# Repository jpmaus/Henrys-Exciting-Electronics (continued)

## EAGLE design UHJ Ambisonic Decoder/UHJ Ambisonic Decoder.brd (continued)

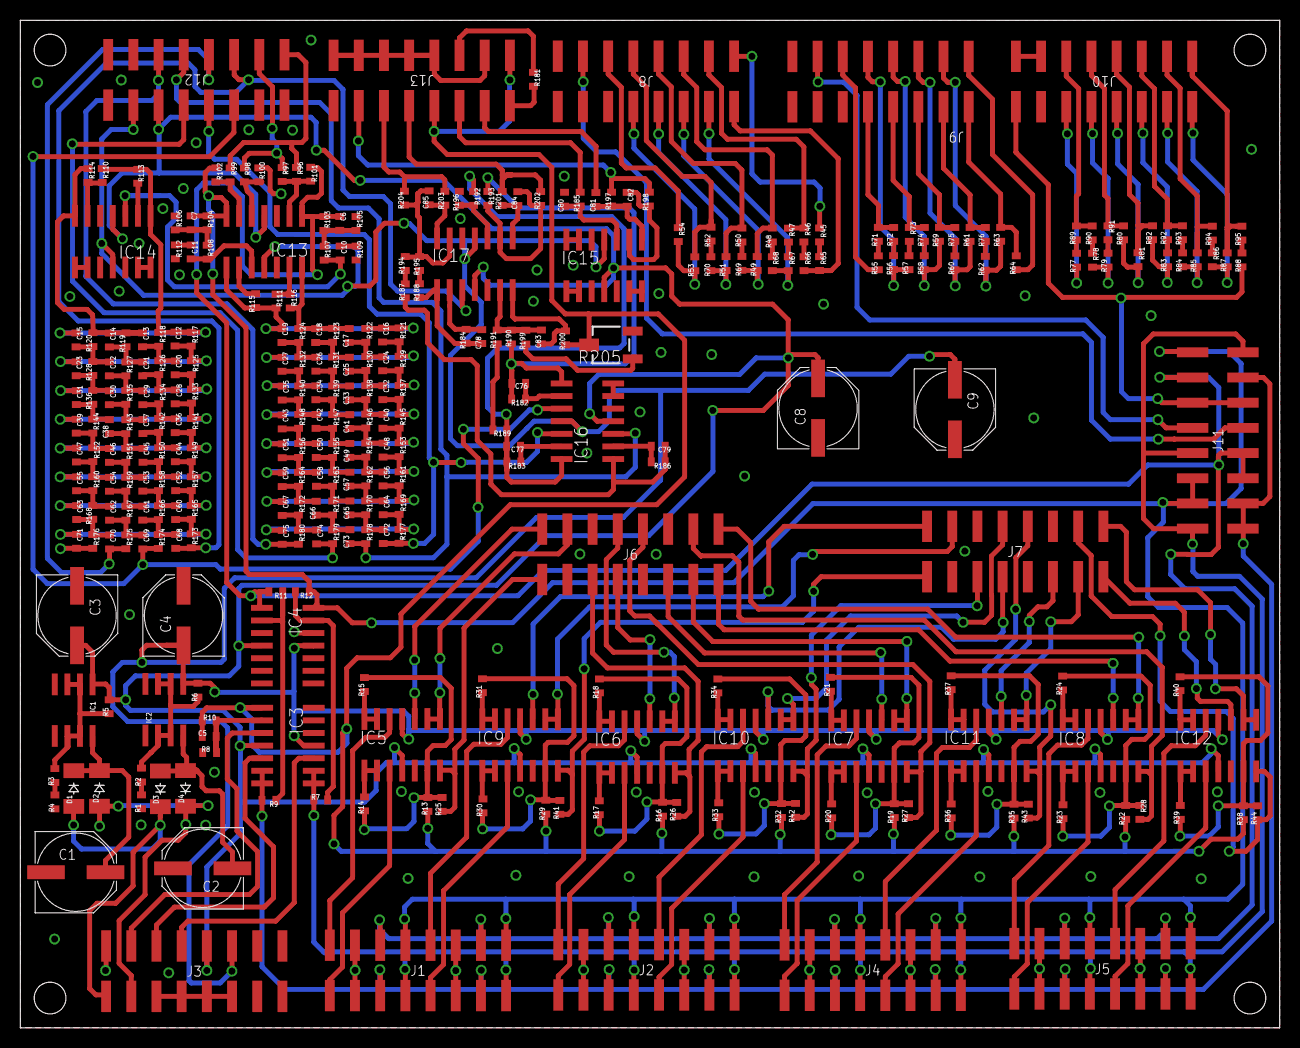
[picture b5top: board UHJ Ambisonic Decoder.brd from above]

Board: 2 copper layers, 127.0 x 101.6 mm, 324 parts (0 on the bottom side), 261 nets.

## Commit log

2020-09-21 Create UHJ Ambisonic Decoder
2020-09-21 Create Dual Analogue Frequency Shifter
2020-09-21 Create Itchycoo Tape Flanger
2020-09-21 Create Oscillator Or Joystick Ambisonic Pan-Rotate
2020-09-21 Create Ambisonic "Clock" Decoder With Phase Shifted Crosstalk Cancellation
2020-09-21 Create images
